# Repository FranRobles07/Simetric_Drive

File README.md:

# Simetric_Drive
vitacora de un proyecto acerca de un volante para videojuegos y simuladores

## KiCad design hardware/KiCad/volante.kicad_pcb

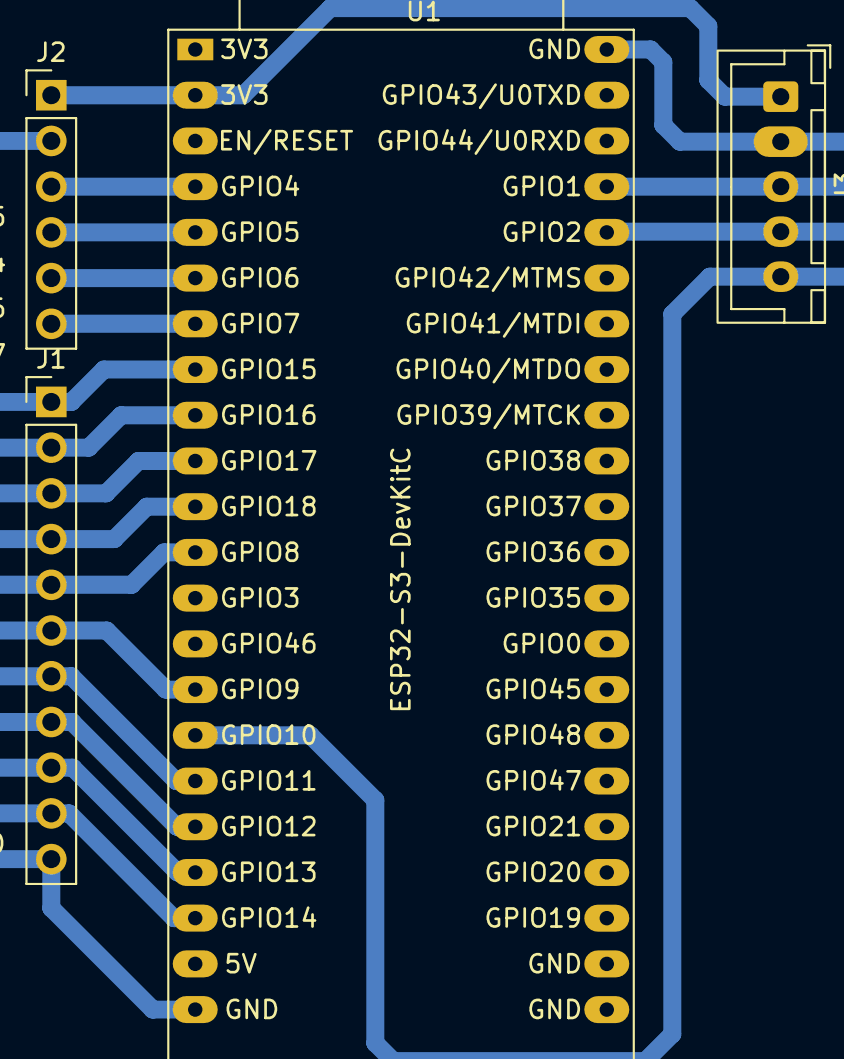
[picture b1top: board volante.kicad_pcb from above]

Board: 2 copper layers, 21 parts (0 on the bottom side), 19 nets.

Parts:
C1, C2, C3, C4, C5, C6, C7, C8, C9, C10, C11, C12, C13, C14, C15, C16, C17: 100nf; C_0805_2012Metric
J1: pinera_switches; PinHeader_1x11_P2.54mm_Vertical
J2: pineras_pote_volante; PinHeader_1x06_P2.54mm_Vertical
J3: pineras_pote_pedales; JST_XH_B5B-XH-A_1x05_P2.50mm_Vertical
U1: ESP32-S3-DevKitC

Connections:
+3.3V: J2.1, J3.1, U1.1 (3V3), U1.2 (3V3)
/GND: C1.2, C2.2, C3.2, C4.2, C5.2, C6.2, C7.2, C8.2, C9.2, C10.2, C11.2, C12.2, C13.2, C14.2, C15.2, C16.2, C17.2, J1.11, J2.2, J3.2, U1.22 (GND), U1.23 (GND), U1.24 (GND), U1.44 (GND)
/GPIO1: C11.1, J3.3, U1.41 (GPIO1/ADC1_CH0)
/GPIO2: C12.1, J3.4, U1.40 (GPIO2/ADC1_CH1)
/GPIO4: C15.1, J2.3, U1.4 (GPIO4/ADC1_CH3)
/GPIO5: C14.1, J2.4, U1.5 (GPIO5/ADC1_CH4)
/GPIO6: C16.1, J2.5, U1.6 (GPIO6/ADC1_CH5)
/GPIO7: C17.1, J2.6, U1.7 (GPIO7/ADC1_CH6)
/GPIO8: C5.1, J1.5, U1.12 (GPIO8/ADC1_CH7)
/GPIO9: C6.1, J1.6, U1.15 (GPIO9/ADC1_CH8)
/GPIO10: C13.1, J3.5, U1.16 (GPIO10/ADC1_CH9)
/GPIO11: C7.1, J1.7, U1.17 (GPIO11/ADC2_CH0)
/GPIO12: C8.1, J1.8, U1.18 (GPIO12/ADC2_CH1)
/GPIO13: C9.1, J1.9, U1.19 (GPIO13/ADC2_CH2)
/GPIO14: C10.1, J1.10, U1.20 (GPIO14/ADC2_CH3)
/GPIO15: C1.1, J1.1, U1.8 (GPIO15/ADC2_CH4/32K_P)
/GPIO16: C2.1, J1.2, U1.9 (GPIO16/ADC2_CH5/32K_N)
/GPIO17: C3.1, J1.3, U1.10 (GPIO17/ADC2_CH6)
/GPIO18: C4.1, J1.4, U1.11 (GPIO18/ADC2_CH7)
